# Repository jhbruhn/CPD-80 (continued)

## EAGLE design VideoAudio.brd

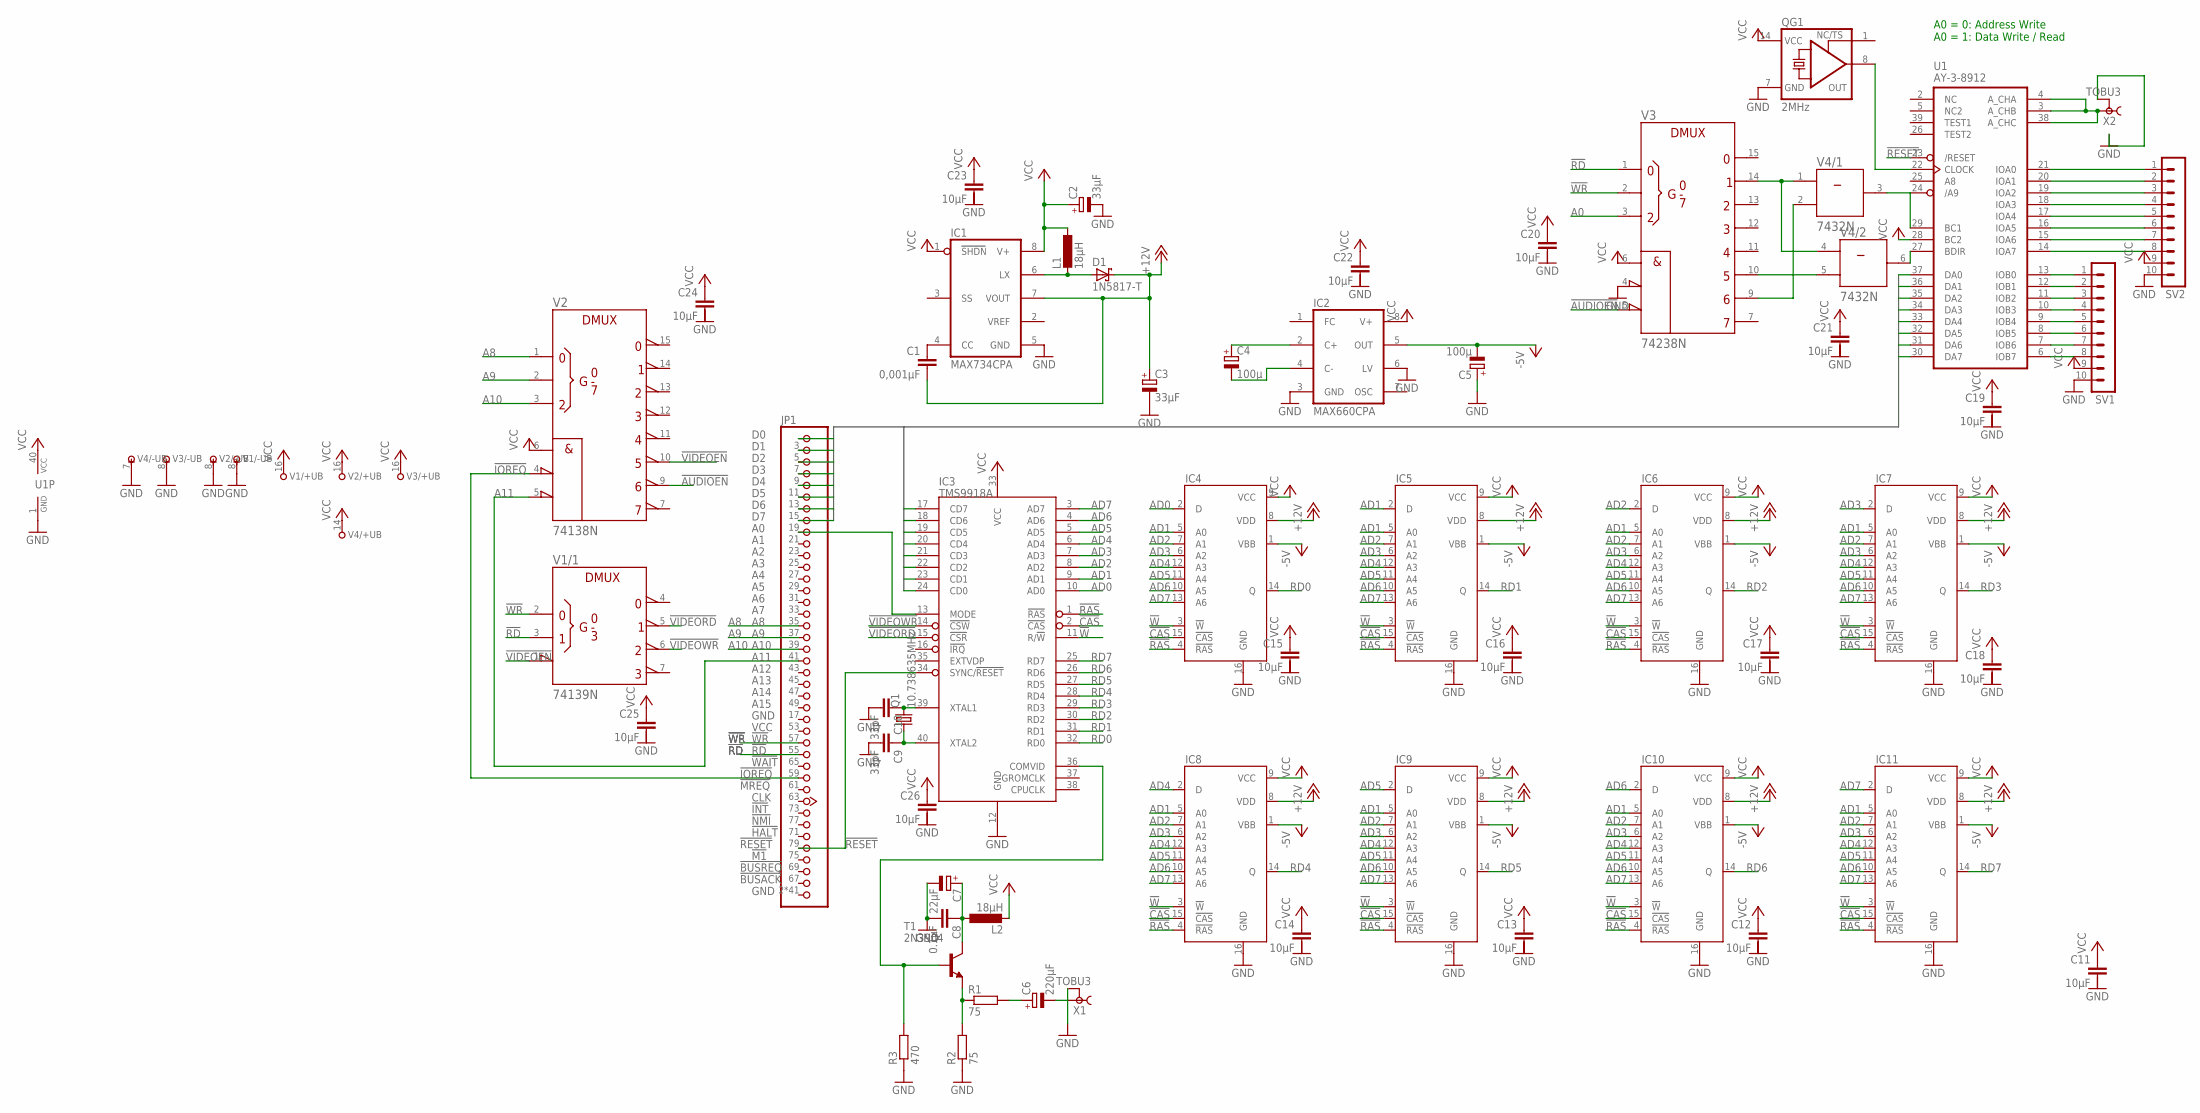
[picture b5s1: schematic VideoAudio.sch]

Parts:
C1: 0,001µF; C050-025X075
C2, C3: 33µF; E2,5-5
C4, C5: 100µ; E2,5-6
C6: 220µF; E2,5-5
C7: 22µF; E2,5-5
C8: 0.1µF; C025-030X050
C9, C10: 33pF; C025-030X050
C11, C12, C13, C14, C15, C16, C17, C18, C19, C20, C21, C22, C23, C24, C25, C26: 10µF; C050-025X075
D1: 1N5817-T; DO41-7.6
IC1: MAX734CPA; DIL08
IC2: MAX660CPA; DIL08
IC3: TMS9918A; DIP40
IC4, IC5, IC6, IC7, IC8, IC9, IC10, IC11: TMS4116; DIL16
JP1: JEANNECTOR/90; 2X25/90
L1, L2: 18µH; 0204/7
Q1: 10.738635MHz; HC49U70
QG1: 2MHz; DIL14S
R1, R2: 75; 0204V
R3: 470; 0204V
SV1, SV2: MA10-1
T1: 2N3904; TO92
U1: AY-3-8912; DIL40
V1: 74139N; DIL16
V2: 74138N; DIL16
V3: 74238N; DIL16
V4: 7432N; DIL14
X1, X2: TOBU3

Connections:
!AUDIOEN: V2.9 (Y6), V3.5 (!G2B)
!CAS: IC3.2 (!CAS), IC4.15 (!CAS), IC5.15 (!CAS), IC6.15 (!CAS), IC7.15 (!CAS), IC8.15 (!CAS), IC9.15 (!CAS), IC10.15 (!CAS), IC11.15 (!CAS)
!IOREQ: JP1.59 (!IOREQ), V2.4 (!G2A)
!RAS: IC3.1 (!RAS), IC4.4 (!RAS), IC5.4 (!RAS), IC6.4 (!RAS), IC7.4 (!RAS), IC8.4 (!RAS), IC9.4 (!RAS), IC10.4 (!RAS), IC11.4 (!RAS)
!RD: JP1.55 (!RD), V1.3 (B), V3.1 (A)
!RESET: IC3.34 (SYNC/!RESET), JP1.79 (!RESET), U1.23 (/RESET)
!VIDEOEN: V1.1 (!G), V2.10 (Y5)
!VIDEORD: IC3.15 (!CSR), V1.5 (Y1)
!VIDEOWR: IC3.14 (!CSW), V1.6 (Y2)
!W: IC3.11 (R/!W), IC4.3 (!W), IC5.3 (!W), IC6.3 (!W), IC7.3 (!W), IC8.3 (!W), IC9.3 (!W), IC10.3 (!W), IC11.3 (!W)
!WR: JP1.57 (!WR), V1.2 (A), V3.2 (B)
+12V: C1.2, C3.+, D1.C, IC1.7 (VOUT), IC4.8 (VDD), IC5.8 (VDD), IC6.8 (VDD), IC7.8 (VDD), IC8.8 (VDD), IC9.8 (VDD), IC10.8 (VDD), IC11.8 (VDD)
-5V: C5.-, IC2.5 (OUT), IC4.1 (VBB), IC5.1 (VBB), IC6.1 (VBB), IC7.1 (VBB), IC8.1 (VBB), IC9.1 (VBB), IC10.1 (VBB), IC11.1 (VBB)
A0: V3.3 (C)
A8: JP1.35 (A8), V2.1 (A)
A9: JP1.37 (A9), V2.2 (B)
A10: JP1.39 (A10), V2.3 (C)
A11: JP1.41 (A11), V2.5 (!G2B)
AD0: IC3.10 (AD0), IC4.2 (D)
AD1: IC3.9 (AD1), IC4.5 (A0), IC5.2 (D), IC5.5 (A0), IC6.5 (A0), IC7.5 (A0), IC8.5 (A0), IC9.5 (A0), IC10.5 (A0), IC11.5 (A0)
AD2: IC3.8 (AD2), IC4.7 (A1), IC5.7 (A1), IC6.2 (D), IC6.7 (A1), IC7.7 (A1), IC8.7 (A1), IC9.7 (A1), IC10.7 (A1), IC11.7 (A1)
AD3: IC3.7 (AD3), IC4.6 (A2), IC5.6 (A2), IC6.6 (A2), IC7.2 (D), IC7.6 (A2), IC8.6 (A2), IC9.6 (A2), IC10.6 (A2), IC11.6 (A2)
AD4: IC3.6 (AD4), IC4.12 (A3), IC5.12 (A3), IC6.12 (A3), IC7.12 (A3), IC8.2 (D), IC8.12 (A3), IC9.12 (A3), IC10.12 (A3), IC11.12 (A3)
AD5: IC3.5 (AD5), IC4.11 (A4), IC5.11 (A4), IC6.11 (A4), IC7.11 (A4), IC8.11 (A4), IC9.2 (D), IC9.11 (A4), IC10.11 (A4), IC11.11 (A4)
AD6: IC3.4 (AD6), IC4.10 (A5), IC5.10 (A5), IC6.10 (A5), IC7.10 (A5), IC8.10 (A5), IC9.10 (A5), IC10.2 (D), IC10.10 (A5), IC11.10 (A5)
AD7: IC3.3 (AD7), IC4.13 (A6), IC5.13 (A6), IC6.13 (A6), IC7.13 (A6), IC8.13 (A6), IC9.13 (A6), IC10.13 (A6), IC11.2 (D), IC11.13 (A6)
D0: IC3.24 (CD0), JP1.1 (D0), U1.37 (DA0)
D1: IC3.23 (CD1), JP1.3 (D1), U1.36 (DA1)
D2: IC3.22 (CD2), JP1.5 (D2), U1.35 (DA2)
D3: IC3.21 (CD3), JP1.7 (D3), U1.34 (DA3)
D4: IC3.20 (CD4), JP1.9 (D4), U1.33 (DA4)
D5: IC3.19 (CD5), JP1.11 (D5), U1.32 (DA5)
D6: IC3.18 (CD6), JP1.13 (D6), U1.31 (DA6)
D7: IC3.17 (CD7), JP1.15 (D7), U1.30 (DA7)
GND: C2.-, C3.-, C5.+, C7.-, C8.2, C9.2, C10.2, IC1.5 (GND), IC2.3 (GND), IC2.6 (LV), IC3.12 (GND), IC4.16 (GND), IC5.16 (GND), IC6.16 (GND), IC7.16 (GND), IC8.16 (GND), IC9.16 (GND), IC10.16 (GND), IC11.16 (GND), JP1.2 (GND), JP1.4 (GND), JP1.6 (GND), JP1.8 (GND), JP1.10 (GND), JP1.12 (GND), JP1.14 (GND), JP1.16 (GND), JP1.17 (GND), JP1.18 (GND), JP1.20 (GND), JP1.22 (GND), JP1.24 (GND), JP1.26 (GND), JP1.28 (GND), JP1.30 (GND), JP1.32 (GND), JP1.34 (GND), JP1.36 (GND), JP1.38 (GND), JP1.40 (GND), JP1.42 (GND), JP1.44 (GND), JP1.46 (GND), JP1.48 (GND), JP1.50 (GND), JP1.51 (GND), JP1.52 (GND), JP1.54 (GND), JP1.56 (GND), JP1.58 (GND), JP1.60 (GND), JP1.62 (GND), JP1.64 (GND), JP1.66 (GND), JP1.68 (GND), JP1.70 (GND), JP1.72 (GND), JP1.74 (GND), JP1.76 (GND), JP1.78 (GND), JP1.80 (GND), QG1.7 (GND), R2.1, R3.1, SV1.10, SV2.10, U1.1 (GND), V1.8 (-UB), V2.8 (-UB), V3.4 (!G2A), V3.8 (-UB), V4.7 (-UB), X1.2, X1.2@1 (2), X1.2@2 (2), X2.2, X2.2@1 (2), X2.2@2 (2)
unnamed: C4.-, IC2.4 (C-)
unnamed: C4.+, IC2.2 (C+)
unnamed: D1.A, IC1.6 (LX), L1.2
unnamed: C1.1, IC1.4 (CC)
unnamed: IC3.13 (MODE), JP1.19 (A0)
unnamed: U1.3 (A_CHB), U1.4 (A_CHA), U1.38 (A_CHC), X2.1
unnamed: C6.-, X1.1
unnamed: C6.+, R1.2
unnamed: R1.1, R2.2, T1.3 (E)
unnamed: IC3.36 (COMVID), R3.2, T1.2 (B)
unnamed: V3.9 (Y6), V4.2 (B)
unnamed: C7.+, C8.1, L2.1, T1.1 (C)
unnamed: C10.1, IC3.39 (XTAL1), Q1.2
unnamed: C9.1, IC3.40 (XTAL2), Q1.1
unnamed: U1.29 (BC1), V4.3 (Y)
unnamed: V3.14 (Y1), V4.1 (A), V4.4 (A)
unnamed: U1.27 (BDIR), V4.6 (Y)
unnamed: V3.10 (Y5), V4.5 (B)
unnamed: SV1.1, U1.13 (IOB0)
unnamed: SV1.2, U1.12 (IOB1)
unnamed: SV1.3, U1.11 (IOB2)
unnamed: SV1.4, U1.10 (IOB3)
unnamed: SV1.5, U1.9 (IOB4)
unnamed: SV1.6, U1.8 (IOB5)
unnamed: SV1.7, U1.7 (IOB6)
unnamed: SV1.8, U1.6 (IOB7)
unnamed: QG1.8 (OUT), U1.22 (CLOCK)
unnamed: SV2.1, U1.21 (IOA0)
unnamed: SV2.2, U1.20 (IOA1)
unnamed: SV2.3, U1.19 (IOA2)
unnamed: SV2.4, U1.18 (IOA3)
unnamed: SV2.5, U1.17 (IOA4)
unnamed: SV2.6, U1.16 (IOA5)
unnamed: SV2.7, U1.15 (IOA6)
unnamed: SV2.8, U1.14 (IOA7)
RD0: IC3.32 (RD0), IC4.14 (Q)
RD1: IC3.31 (RD1), IC5.14 (Q)
RD2: IC3.30 (RD2), IC6.14 (Q)
RD3: IC3.29 (RD3), IC7.14 (Q)
RD4: IC3.28 (RD4), IC8.14 (Q)
RD5: IC3.27 (RD5), IC9.14 (Q)
RD6: IC3.26 (RD6), IC10.14 (Q)
RD7: IC3.25 (RD7), IC11.14 (Q)
VCC: C2.+, C11.1, C12.1, C13.1, C14.1, C15.1, C16.1, C17.1, C18.1, C19.1, C20.1, C21.1, C22.1, C23.1, C24.1, C25.1, C26.1, IC1.1 (SHDN), IC1.8 (V+), IC2.8 (V+), IC3.33 (VCC), IC4.9 (VCC), IC5.9 (VCC), IC6.9 (VCC), IC7.9 (VCC), IC8.9 (VCC), IC9.9 (VCC), IC10.9 (VCC), IC11.9 (VCC), JP1.53 (VCC), L1.1, L2.2, QG1.14 (VCC), SV1.9, SV2.9, U1.28 (BC2), U1.40 (VCC), V1.16 (+UB), V2.6 (G1), V2.16 (+UB), V3.6 (G1), V3.16 (+UB), V4.14 (+UB)

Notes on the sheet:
A0 = 0: Address Write A0 = 1: Data Write / Read

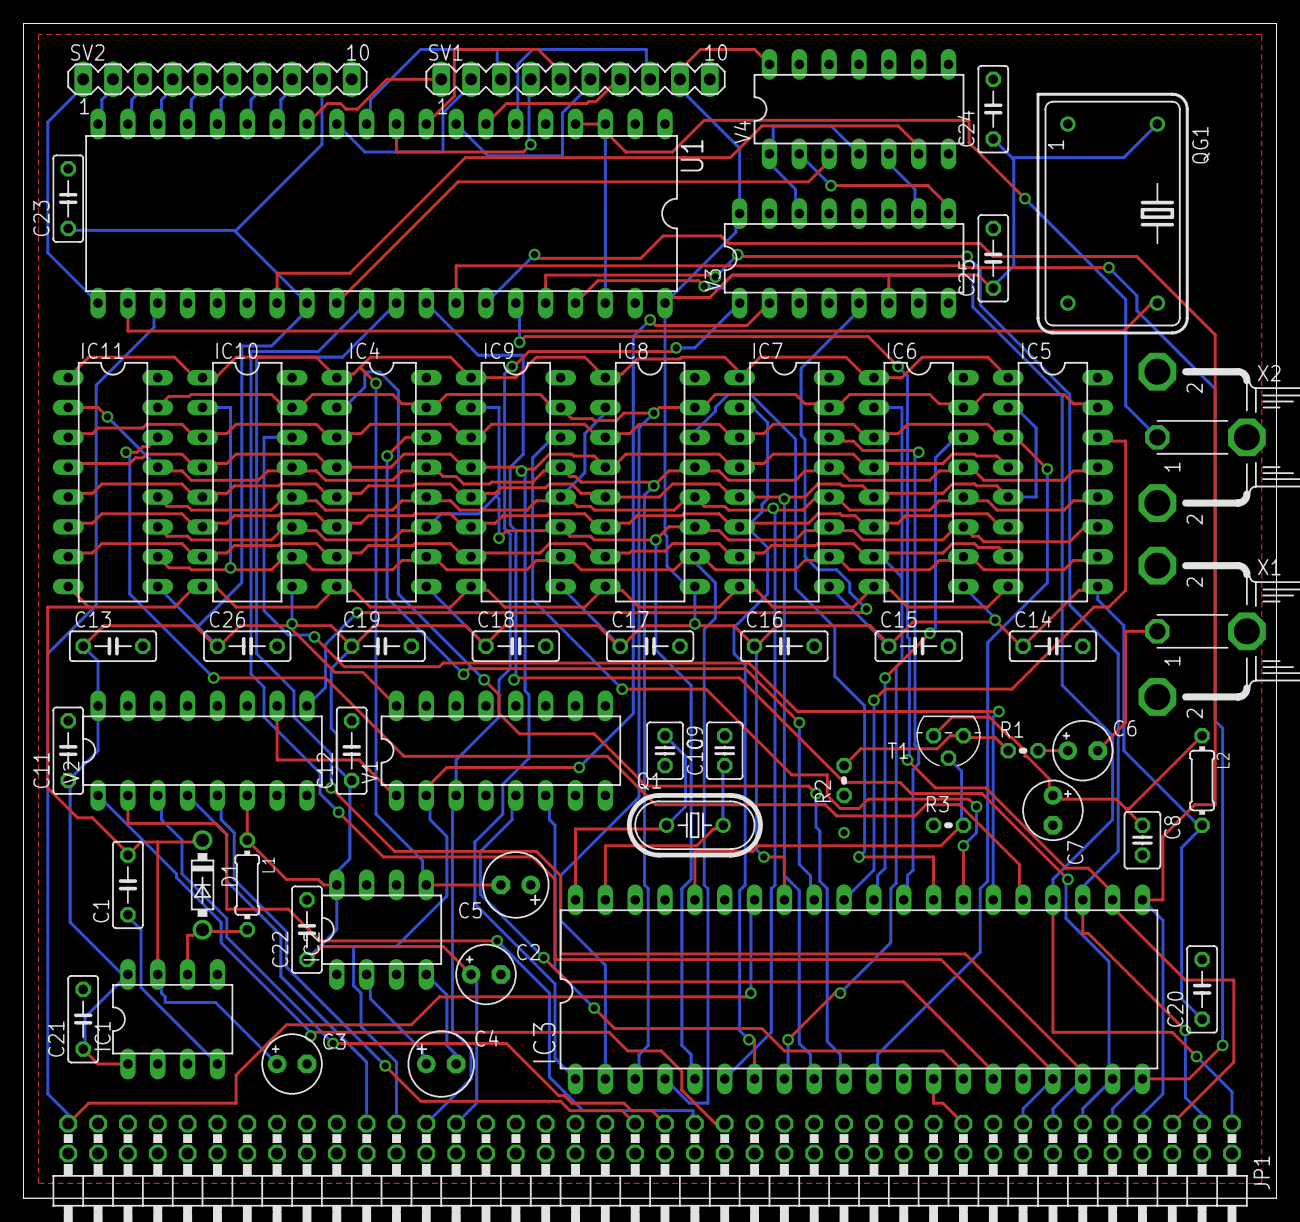
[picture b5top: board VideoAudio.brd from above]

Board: 2 copper layers, 106.7 x 100.0 mm, 56 parts (0 on the bottom side), 78 nets.

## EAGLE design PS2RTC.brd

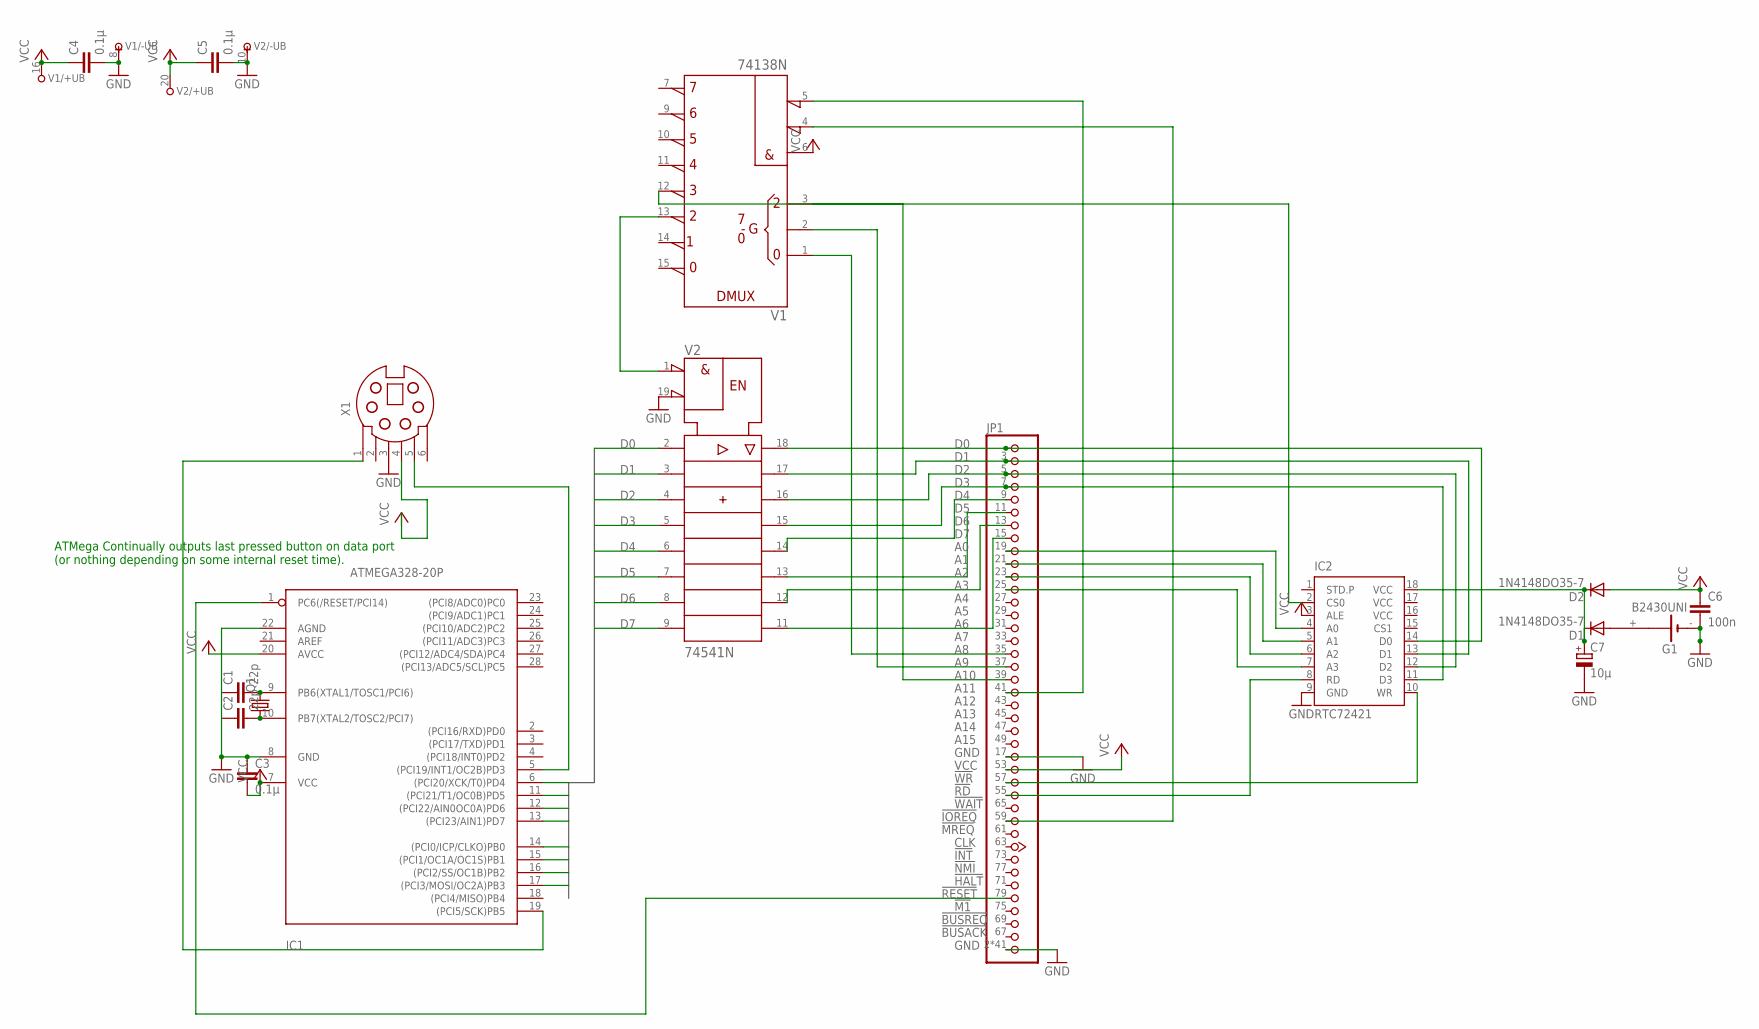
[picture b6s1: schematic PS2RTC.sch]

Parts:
C1, C2: 22p; C5B3
C3, C4, C5: 0.1µ; C5B3
C6: 100n; C2.5-2
C7: 10µ; E2-4
D1, D2: 1N4148DO35-7; DO35-7
G1: B2430UNI
IC1: ATMEGA328-20P; DIL28-3
IC2: RTC72421; DIL18
JP1: JEANNECTOR/90; 2X25/90
Q1: CRYSTALHC49S; HC49/S
V1: 74138N; DIL16
V2: 74541N; DIL20
X1: MDSSV-F06; SSV-BC06

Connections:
D0: IC1.6 ((PCI20/XCK/T0)PD4), V2.2 (A1)
D1: IC1.11 ((PCI21/T1/OC0B)PD5), V2.3 (A2)
D2: IC1.12 ((PCI22/AIN0OC0A)PD6), V2.4 (A3)
D3: IC1.13 ((PCI23/AIN1)PD7), V2.5 (A4)
D4: IC1.14 ((PCI0/ICP/CLKO)PB0), V2.6 (A5)
D5: IC1.15 ((PCI1/OC1A/OC1S)PB1), V2.7 (A6)
D6: IC1.16 ((PCI2/SS/OC1B)PB2), V2.8 (A7)
D7: IC1.17 ((PCI3/MOSI/OC2A)PB3), V2.9 (A8)
GND: C3.1, C4.2, C5.2, C6.2, C7.-, G1.-, IC1.8 (GND), IC1.22 (AGND), IC2.9 (GND), JP1.2 (GND), JP1.4 (GND), JP1.6 (GND), JP1.8 (GND), JP1.10 (GND), JP1.12 (GND), JP1.14 (GND), JP1.16 (GND), JP1.17 (GND), JP1.18 (GND), JP1.20 (GND), JP1.22 (GND), JP1.24 (GND), JP1.26 (GND), JP1.28 (GND), JP1.30 (GND), JP1.32 (GND), JP1.34 (GND), JP1.36 (GND), JP1.38 (GND), JP1.40 (GND), JP1.42 (GND), JP1.44 (GND), JP1.46 (GND), JP1.48 (GND), JP1.50 (GND), JP1.51 (GND), JP1.52 (GND), JP1.54 (GND), JP1.56 (GND), JP1.58 (GND), JP1.60 (GND), JP1.62 (GND), JP1.64 (GND), JP1.66 (GND), JP1.68 (GND), JP1.70 (GND), JP1.72 (GND), JP1.74 (GND), JP1.76 (GND), JP1.78 (GND), JP1.80 (GND), V1.8 (-UB), V2.10 (-UB), V2.19 (!G2), X1.3
unnamed: JP1.35 (A8), V1.1 (A)
unnamed: JP1.37 (A9), V1.2 (B)
unnamed: JP1.39 (A10), V1.3 (C)
unnamed: IC1.5 ((PCI19/INT1/OC2B)PD3), X1.5
unnamed: V1.13 (Y2), V2.1 (!G1)
unnamed: IC1.19 ((PCI5/SCK)PB5), X1.1
unnamed: JP1.59 (!IOREQ), V1.4 (!G2A)
unnamed: JP1.41 (A11), V1.5 (!G2B)
unnamed: IC2.14 (D0), JP1.1 (D0), V2.18 (Y1)
unnamed: IC2.13 (D1), JP1.3 (D1), V2.17 (Y2)
unnamed: IC2.12 (D2), JP1.5 (D2), V2.16 (Y3)
unnamed: IC2.11 (D3), JP1.7 (D3), V2.15 (Y4)
unnamed: JP1.9 (D4), V2.14 (Y5)
unnamed: JP1.11 (D5), V2.13 (Y6)
unnamed: JP1.13 (D6), V2.12 (Y7)
unnamed: JP1.15 (D7), V2.11 (Y8)
unnamed: IC1.1 (PC6(/RESET/PCI14)), JP1.79 (!RESET)
unnamed: C1.2, IC1.9 (PB6(XTAL1/TOSC1/PCI6)), Q1.2
unnamed: C2.2, IC1.10 (PB7(XTAL2/TOSC2/PCI7)), Q1.1
unnamed: D1.A, G1.+
unnamed: IC2.4 (A0), JP1.19 (A0)
unnamed: IC2.5 (A1), JP1.21 (A1)
unnamed: C7.+, D1.C, D2.C, IC2.18 (VCC)
unnamed: IC2.6 (A2), JP1.23 (A2)
unnamed: IC2.7 (A3), JP1.25 (A3)
unnamed: IC2.8 (RD), JP1.55 (!RD)
unnamed: IC2.10 (WR), JP1.57 (!WR)
unnamed: IC2.2 (CS0), V1.12 (Y3)
VCC: C3.2, C4.1, C5.1, C6.1, D2.A, IC1.7 (VCC), IC1.20 (AVCC), IC2.3 (ALE), IC2.16 (VCC), IC2.17 (VCC), JP1.53 (VCC), V1.6 (G1), V1.16 (+UB), V2.20 (+UB), X1.4

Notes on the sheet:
ATMega Continually outputs last pressed button on data port (or nothing depending on some internal reset time).

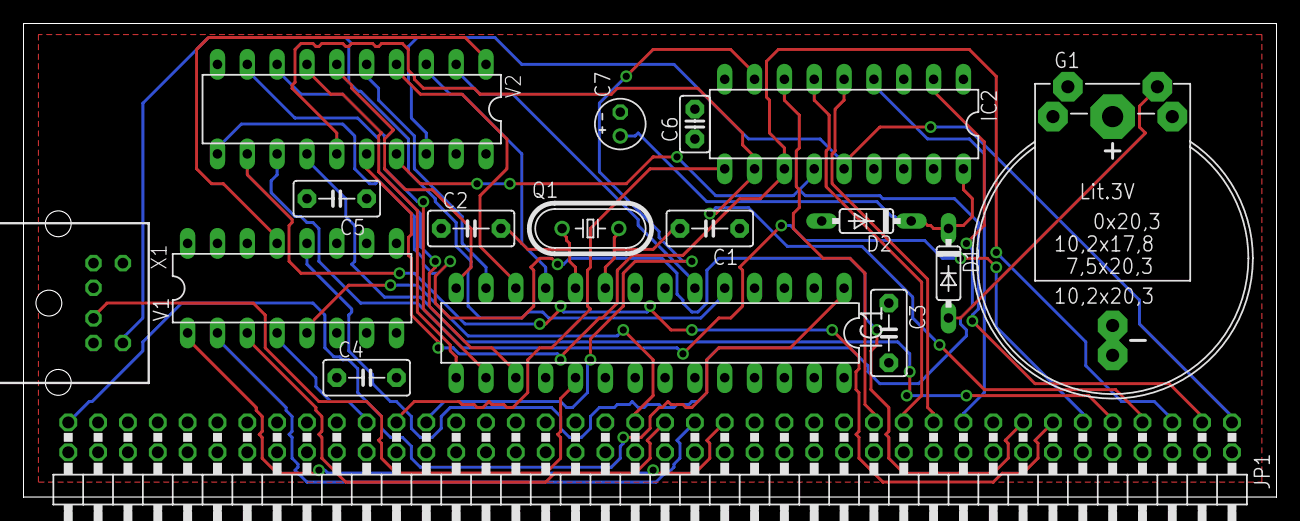
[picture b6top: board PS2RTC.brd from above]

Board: 2 copper layers, 106.7 x 40.3 mm, 17 parts (0 on the bottom side), 38 nets.

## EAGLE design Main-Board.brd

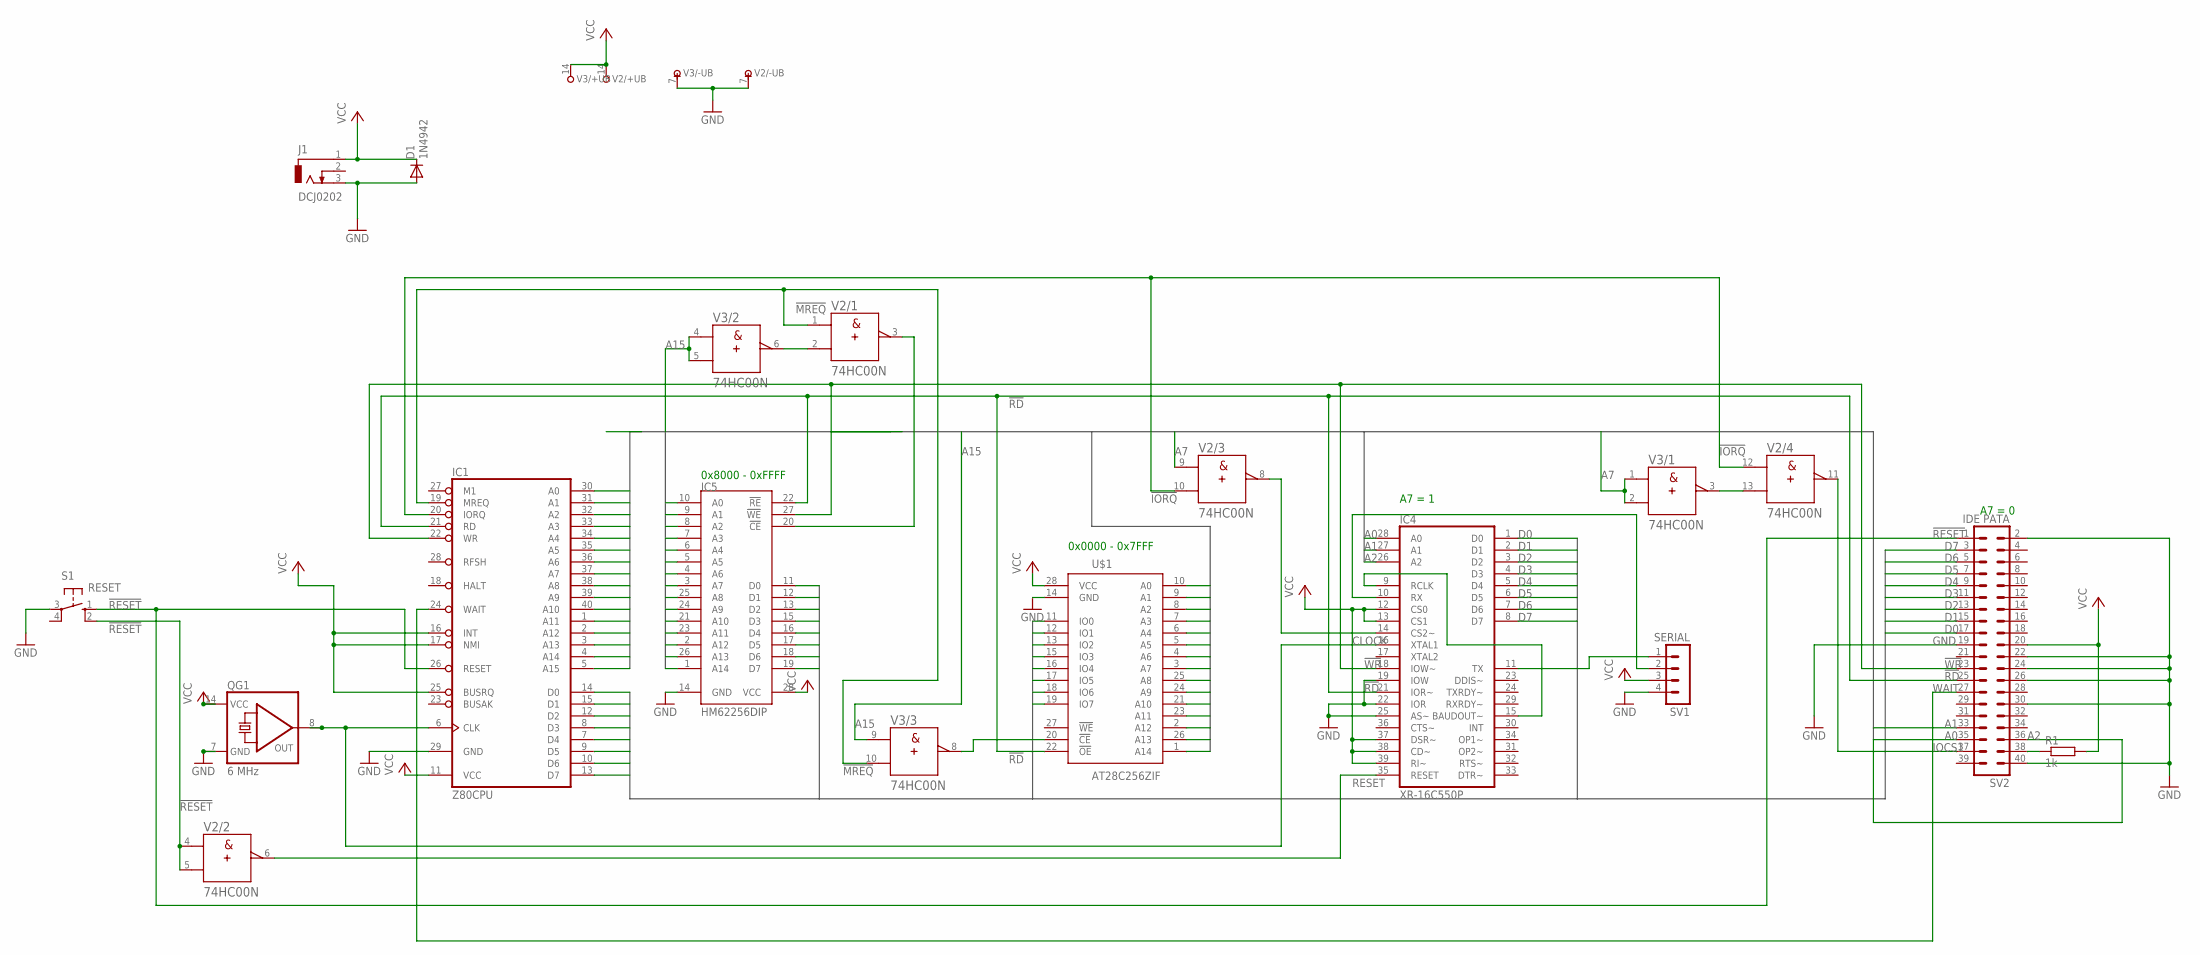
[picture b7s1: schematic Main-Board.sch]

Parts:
D1: 1N4942; DO41-10; MPN 1N4935G
IC1: Z80CPU; DIL40
IC4: XR-16C550P; DIL40
IC5: HM62256DIP; HM62256-DIP
J1: DCJ0202
QG1: 6 MHz; DIL14S
R1: 1k; 0207/10; MPN MCRE000037
S1: RESET; B3F-10XX
SV1: SERIAL; MA04-1
SV2: IDE PATA; MA20-2
U$1: AT28C256ZIF; DIL28-ZIF
V2, V3: 74HC00N; DIL14; MPN SN74HC00N

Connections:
!IORQ: IC1.20 (IORQ), V2.10 (B), V2.12 (A)
!MREQ: IC1.19 (MREQ), V2.1 (A), V3.10 (B)
!RD: IC1.21 (RD), IC4.21 (IOR~), IC5.22 (!RE), SV2.25, U$1.22 (!OE)
!RESET: IC1.26 (RESET), S1.1 (S), S1.2 (S1), SV2.1, V2.4 (A), V2.5 (B)
!WR: IC1.22 (WR), IC4.18 (IOW~), IC5.27 (!WE), SV2.23
A0: IC1.30 (A0), IC4.28 (A0), IC5.10 (A0), SV2.35, U$1.10 (A0)
A1: IC1.31 (A1), IC4.27 (A1), IC5.9 (A1), SV2.33, U$1.9 (A1)
A2: IC1.32 (A2), IC4.26 (A2), IC5.8 (A2), SV2.36, U$1.8 (A2)
A3: IC1.33 (A3), IC5.7 (A3), U$1.7 (A3)
A4: IC1.34 (A4), IC5.6 (A4), U$1.6 (A4)
A5: IC1.35 (A5), IC5.5 (A5), U$1.5 (A5)
A6: IC1.36 (A6), IC5.4 (A6), U$1.4 (A6)
A7: IC1.37 (A7), IC5.3 (A7), U$1.3 (A7), V2.9 (A), V3.1 (A), V3.2 (B)
A8: IC1.38 (A8), IC5.25 (A8), U$1.25 (A8)
A9: IC1.39 (A9), IC5.24 (A9), U$1.24 (A9)
A10: IC1.40 (A10), IC5.21 (A10), U$1.21 (A10)
A11: IC1.1 (A11), IC5.23 (A11), U$1.23 (A11)
A12: IC1.2 (A12), IC5.2 (A12), U$1.2 (A12)
A13: IC1.3 (A13), IC5.26 (A13), U$1.26 (A13)
A14: IC1.4 (A14), IC5.1 (A14), U$1.1 (A14)
A15: IC1.5 (A15), V3.4 (A), V3.5 (B), V3.9 (A)
CLOCK: IC1.6 (CLK), IC4.16 (XTAL1), QG1.8 (OUT)
D0: IC1.14 (D0), IC4.1 (D0), IC5.11 (D0), SV2.17, U$1.11 (IO0)
D1: IC1.15 (D1), IC4.2 (D1), IC5.12 (D1), SV2.15, U$1.12 (IO1)
D2: IC1.12 (D2), IC4.3 (D2), IC5.13 (D2), SV2.13, U$1.13 (IO2)
D3: IC1.8 (D3), IC4.4 (D3), IC5.15 (D3), SV2.11, U$1.15 (IO3)
D4: IC1.7 (D4), IC4.5 (D4), IC5.16 (D4), SV2.9, U$1.16 (IO4)
D5: IC1.9 (D5), IC4.6 (D5), IC5.17 (D5), SV2.7, U$1.17 (IO5)
D6: IC1.10 (D6), IC4.7 (D6), IC5.18 (D6), SV2.5, U$1.18 (IO6)
D7: IC1.13 (D7), IC4.8 (D7), IC5.19 (D7), SV2.3, U$1.19 (IO7)
GND: D1.A, IC1.29 (GND), IC4.19 (IOW), IC4.20 (GND), IC4.22 (IOR), IC4.25 (AS~), IC5.14 (GND), J1.3, QG1.7 (GND), S1.3, SV1.4, SV2.2, SV2.19, SV2.22, SV2.24, SV2.26, SV2.30, SV2.40, U$1.14 (GND), V2.7 (-UB), V3.7 (-UB)
IOCS1: SV2.37, V2.11 (Y)
unnamed: U$1.20 (!CE), V3.8 (Y)
unnamed: V2.2 (B), V3.6 (Y)
unnamed: IC5.20 (!CE), V2.3 (Y)
unnamed: IC4.11 (TX), SV1.1
unnamed: IC4.9 (RCLK), IC4.15 (BAUDOUT~)
unnamed: IC4.10 (RX), SV1.2
unnamed: V2.13 (B), V3.3 (Y)
unnamed: IC4.14 (CS2~), V2.8 (Y)
unnamed: R1.1, SV2.38
RESET: IC4.35 (RESET), V2.6 (Y)
VCC: D1.C, IC1.11 (VCC), IC1.16 (INT), IC1.17 (NMI), IC1.25 (BUSRQ), IC4.12 (CS0), IC4.13 (CS1), IC4.37 (DSR~), IC4.38 (CD~), IC4.39 (RI~), IC4.40 (VCC), IC5.28 (VCC), J1.1, QG1.14 (VCC), R1.2, SV1.3, SV2.20, U$1.28 (VCC), V2.14 (+UB), V3.14 (+UB)
WAIT: IC1.24 (WAIT), SV2.27

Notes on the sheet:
0x0000 - 0x7FFF
0x8000 - 0xFFFF
A7 = 1
A7 = 0

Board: 2 copper layers, 13 parts (0 on the bottom side), 44 nets, no tracks yet.

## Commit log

2017-01-22 :octocat: Added .gitattributes & .gitignore files
2017-01-22 Add Readme, Add Wait line for IO
2017-01-22 Add Z80 to Feature List
2017-01-22 Add Image of Circuit
2017-01-23 Start Splitting into multiple boards
2017-01-24 Connect ROM WriteEnable so we can rewrite rom from the CPU
2017-01-24 Move away Serial CF
2017-01-24 Finish Modularization
2017-01-25 Update names and font
2017-01-25 Add Resistor Value
2017-01-25 Add Interrupt connection for 16550
2017-01-25 Change Memoryboard
2017-01-25 Fix MUDDI. Change values to mm.
2017-01-26 Add Decoupling Capacitors.
2017-01-26 Add missing | to readme
2017-01-26 Change addressbus to allow more devices on it.
2017-01-26 Add Ground Rail to JEANNECTOR
2017-01-27 Make Top Plane a VCC Plane instead of Ground, add Holes
2017-01-27 Add License, fix Markdown formatting
2017-01-27 Add Future Text
2017-01-27 Remove Old Circuit Diagram
2017-01-27 Add Schematic Pictures
2017-01-28 Correctly wire the Enable on SerialCF 74138
2017-01-28 Update SerialCF Picture
2017-01-28 Correctly update serialcf picture
2017-01-28 Add PullUp to reset of cpu
2017-01-28 Use MAX811 for Reset. Add Power Capacitors.
2017-01-28 Fix Memory Mapping inversely. Move Text on Muddi
2017-01-28 Use upper Bits to Address IO devices.
2017-01-28 Update Circuit pictures
2017-01-28 Fix memory mapping issues
2017-01-28 Use LS version for serialCF
2017-01-28 Add PullUps to CPU Board
2017-01-28 Formatting
2017-01-28 Update Muddi Spacing
2017-01-28 Add more mounting holes to muddi
2017-01-28 Remove old gerber files
2017-01-30 Update SerialCF
2017-01-30 Add Experimental PS2 Board.
2017-01-30 Reposition Capacitor
2017-01-30 Extend GND Trace
2017-01-30 Add PS2 Card to readme
2017-01-31 Add RTC to PS2 Board
2017-02-01 Fix incorrectly connected diode
2017-02-01 Added memory ram banking to the memory board
2017-02-01 Add Memory Bank Switch documentation
2017-02-01 Fix Missing VCC and GND Connections
2017-02-02 Added Oscillator to SerialCF Board. And more Serial Pins
2017-02-02 Update Memory
2017-02-02 Update Versions of Memory and SerialCF
2017-02-02 Rearrange Text on Memory Board
2017-02-02 Rearrange Text on SerialCF Board
2017-02-02 Add more Texts
2017-02-13 Restructure CPU Schematic
2017-02-17 Beginn of VideoAudio Board
2017-02-17 Add Video and Audio ports to readme
2017-02-17 Fix Routing Issues with PowerPlanes
2017-02-17 Add Audio and Video to videoboard, not yet ready
2017-02-18 Route Audio/Video Board
2017-03-03 Fix stupid VCC/GND mistakes on Address decoder
2017-06-26 Add software
2017-08-14 Add missing wires
2017-08-17 Add pullup
